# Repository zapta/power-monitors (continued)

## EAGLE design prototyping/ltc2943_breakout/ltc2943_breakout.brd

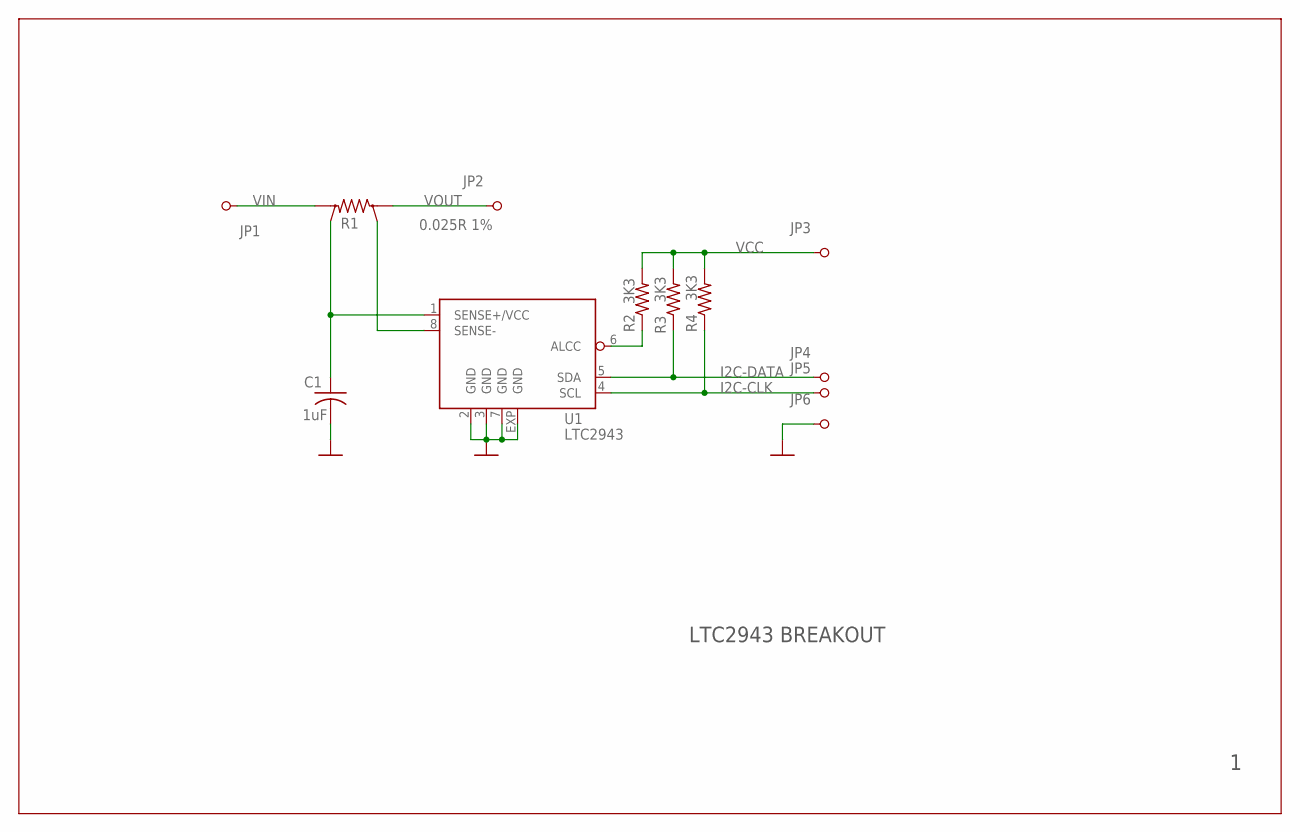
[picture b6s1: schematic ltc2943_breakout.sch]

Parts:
C1: 1uF; C0603
JP1, JP2, JP3, JP4, JP5, JP6: PINHD-1X1; 1X01
R1: 0.025R 1%; KELVIN-6432
R2, R3, R4: 3K3; R0603
U1: LTC2943; DFN8-3X3

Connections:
GND: C1.2, JP6.1, U1.2 (GND), U1.3 (GND), U1.7 (GND), U1.EXP (GND)
I2C-CLK: JP5.1, R4.1, U1.4 (SCL)
I2C-DATA: JP4.1, R3.1, U1.5 (SDA)
unnamed: R2.1, U1.6 (ALCC)
unnamed: R1.V1, U1.8 (SENSE-)
SENSE+: C1.1, R1.V2, U1.1 (SENSE+/VCC)
VCC: JP3.1, R2.2, R3.2, R4.2
VIN: JP1.1, R1.I2
VOUT: JP2.1, R1.I1

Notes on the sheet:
LTC2943 BREAKOUT

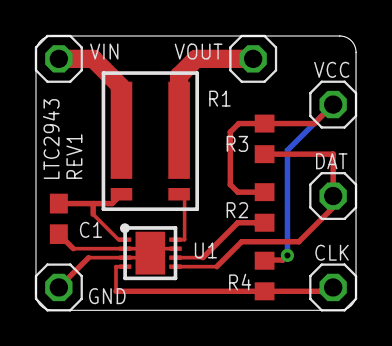
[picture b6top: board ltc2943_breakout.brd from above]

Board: 2 copper layers, 17.8 x 15.2 mm, 12 parts (0 on the bottom side), 9 nets.

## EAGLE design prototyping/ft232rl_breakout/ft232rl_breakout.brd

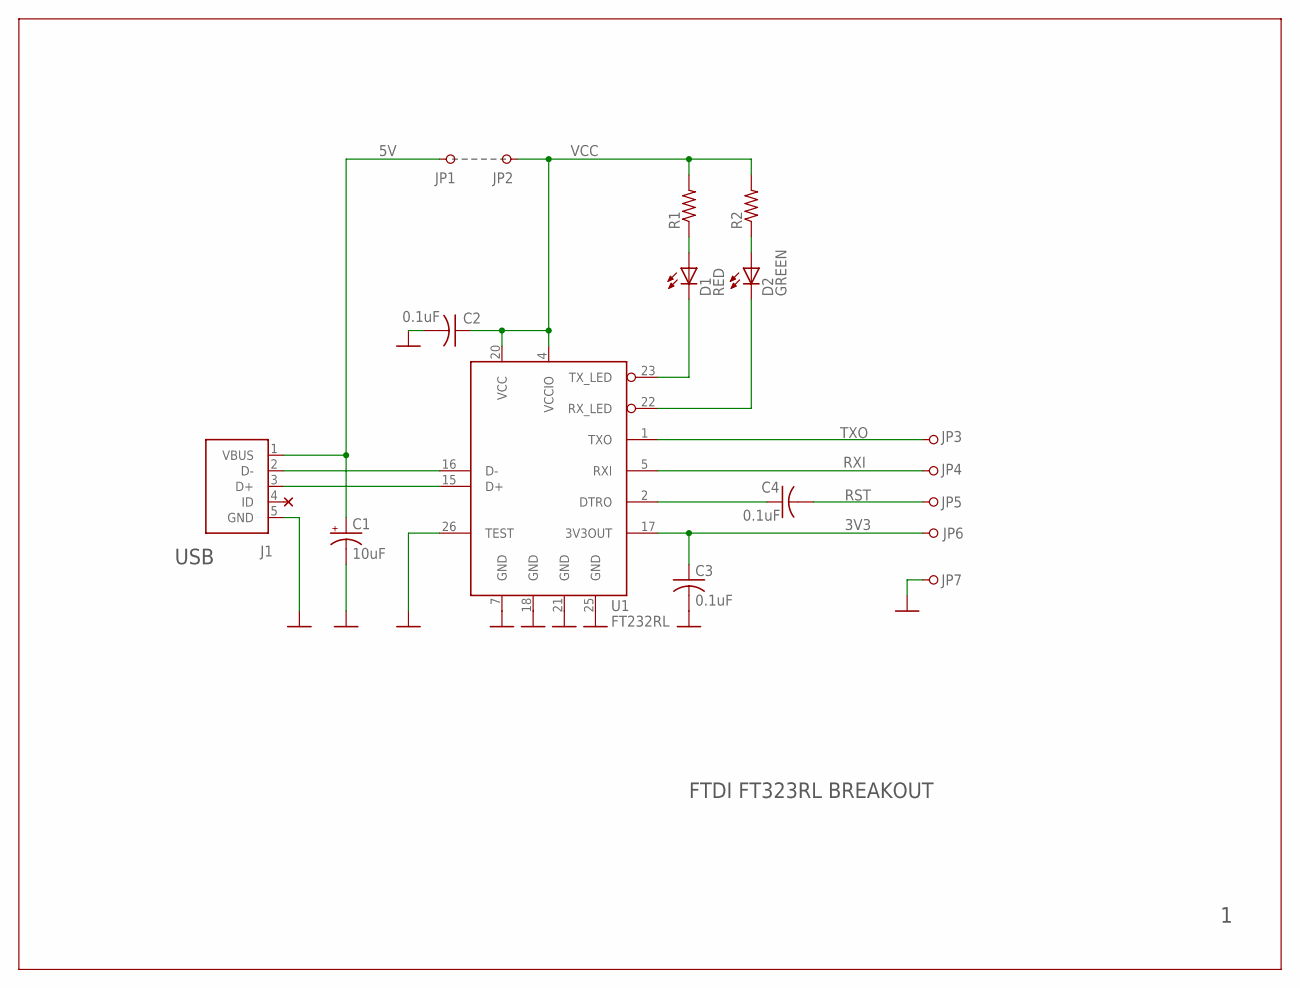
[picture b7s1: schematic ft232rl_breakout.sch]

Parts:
C1: 10uF; A/3216-18R
C2, C3, C4: 0.1uF; C0402K
D1: RED; LED_0402
D2: GREEN; LED_0402
J1: USB; USB-MICRO-ZX62RD-AB-5P8
JP1, JP2, JP3, JP4, JP5, JP6, JP7: PINHD-1X1; 1X01
R1, R2: R-US_R0402; R0402
U1: FT232RL; SSOP28DB

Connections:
3V3: C3.1, JP6.1, U1.17 (3V3OUT)
5V: C1.+, J1.1 (VBUS), JP1.1
GND: C1.-, C2.2, C3.2, J1.5 (GND), JP7.1, U1.7 (GND), U1.18 (GND), U1.21 (GND), U1.25 (GND), U1.26 (TEST)
unnamed: D1.C, U1.23 (TX_LED)
unnamed: D2.C, U1.22 (RX_LED)
unnamed: D1.A, R1.1
unnamed: D2.A, R2.1
unnamed: J1.3 (D+), U1.15 (D+)
unnamed: C4.1, U1.2 (DTRO)
unnamed: J1.2 (D-), U1.16 (D-)
RST: C4.2, JP5.1
RXI: JP4.1, U1.5 (RXI)
TXO: JP3.1, U1.1 (TXO)
VCC: C2.1, JP2.1, R1.2, R2.2, U1.4 (VCCIO), U1.20 (VCC)

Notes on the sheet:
FTDI FT323RL BREAKOUT
USB

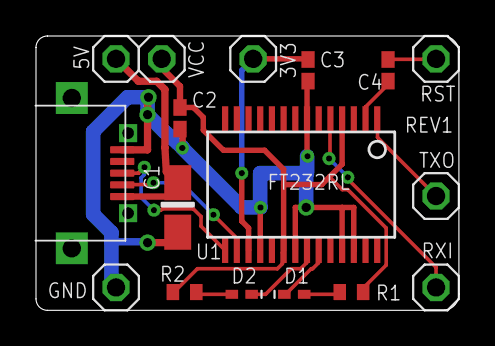
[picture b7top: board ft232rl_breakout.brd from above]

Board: 2 copper layers, 23.5 x 15.2 mm, 17 parts (0 on the bottom side), 14 nets.

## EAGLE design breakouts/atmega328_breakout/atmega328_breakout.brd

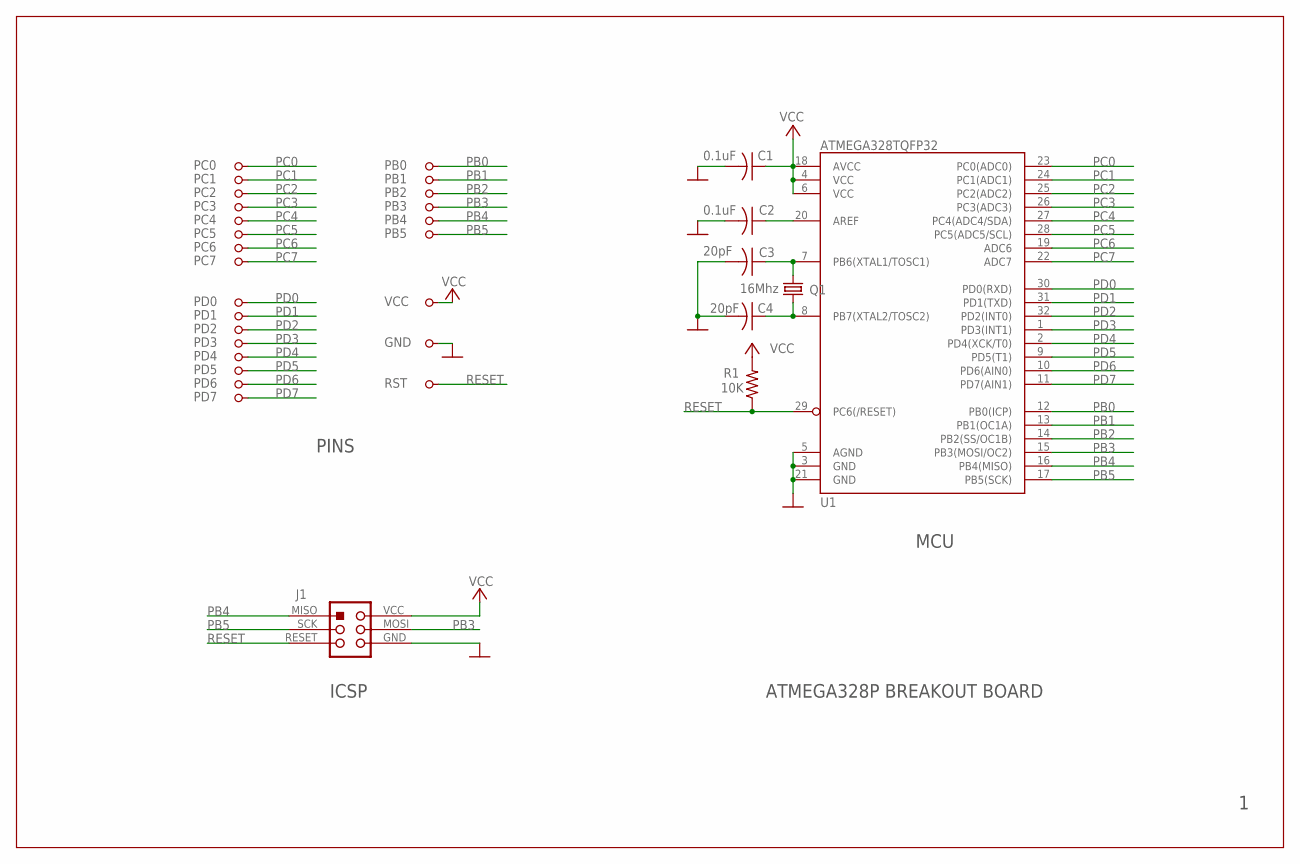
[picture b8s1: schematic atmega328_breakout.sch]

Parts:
C1, C2: 0.1uF; C0603
C3, C4: 20pF; C0603
GND: PINHD-1X1; 1X01
J1: ICSP
PB0, PB1, PB2, PB3, PB4, PB5: PINHD-1X1; 1X01
PC0, PC1, PC2, PC3, PC4, PC5, PC6, PC7: PINHD-1X1; 1X01
PD0, PD1, PD2, PD3, PD4, PD5, PD6, PD7: PINHD-1X1; 1X01
Q1: 16Mhz; CRYSTAL-CTS406
R1: 10K; R0603
RST: PINHD-1X1; 1X01
U1: ATMEGA328TQFP32; TQFP32-08
VCC: PINHD-1X1; 1X01

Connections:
AREF: C2.1, U1.20 (AREF)
GND: C1.2, C2.2, C3.2, C4.2, GND.1, J1.GND, U1.3 (GND), U1.5 (AGND), U1.21 (GND)
unnamed: C3.1, Q1.1, U1.7 (PB6(XTAL1/TOSC1))
unnamed: C4.1, Q1.3 (2), U1.8 (PB7(XTAL2/TOSC2))
PB0: PB0.1, U1.12 (PB0(ICP))
PB1: PB1.1, U1.13 (PB1(OC1A))
PB2: PB2.1, U1.14 (PB2(SS/OC1B))
PB3: J1.MOSI, PB3.1, U1.15 (PB3(MOSI/OC2))
PB4: J1.MISO, PB4.1, U1.16 (PB4(MISO))
PB5: J1.SCK, PB5.1, U1.17 (PB5(SCK))
PC0: PC0.1, U1.23 (PC0(ADC0))
PC1: PC1.1, U1.24 (PC1(ADC1))
PC2: PC2.1, U1.25 (PC2(ADC2))
PC3: PC3.1, U1.26 (PC3(ADC3))
PC4: PC4.1, U1.27 (PC4(ADC4/SDA))
PC5: PC5.1, U1.28 (PC5(ADC5/SCL))
PC6: PC6.1, U1.19 (ADC6)
PC7: PC7.1, U1.22 (ADC7)
PD0: PD0.1, U1.30 (PD0(RXD))
PD1: PD1.1, U1.31 (PD1(TXD))
PD2: PD2.1, U1.32 (PD2(INT0))
PD3: PD3.1, U1.1 (PD3(INT1))
PD4: PD4.1, U1.2 (PD4(XCK/T0))
PD5: PD5.1, U1.9 (PD5(T1))
PD6: PD6.1, U1.10 (PD6(AIN0))
PD7: PD7.1, U1.11 (PD7(AIN1))
RESET: J1.RESET, R1.1, RST.1, U1.29 (PC6(/RESET))
VCC: C1.1, J1.VCC, R1.2, U1.4 (VCC), U1.6 (VCC), U1.18 (AVCC), VCC.1

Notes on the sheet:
ATMEGA328P BREAKOUT BOARD
ICSP
PINS
MCU

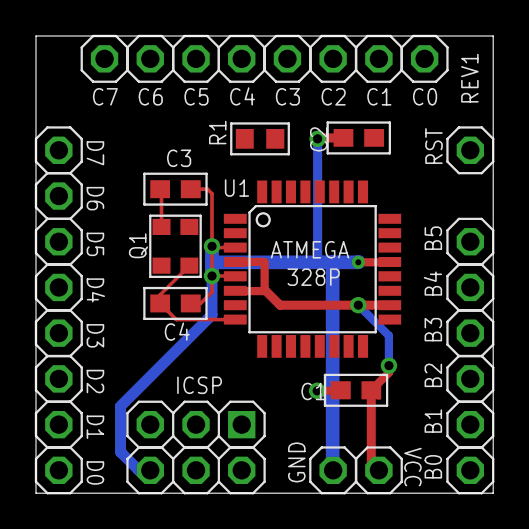
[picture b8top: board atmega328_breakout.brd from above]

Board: 2 copper layers, 25.4 x 25.4 mm, 33 parts (0 on the bottom side), 28 nets.

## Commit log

2014-04-19 Moved files from the temporary repository.
2014-04-19 Renamed eagle files from powermon.* t pmon_uno.*
2014-04-19 Removed the inversion of config input bits. Now using dipswitches that are active when open.
2014-04-19 Replaced dipswitch to through hole. Undone auto routing.
2014-04-19 Added hex image and script to program a blank Pmon Uno.
2014-04-19 Changed board fonts to vector, tweaked text. No final auto routing yet.
2014-04-20 Rearanged the leds pin to have a PWM option for the Status led.
2014-04-20 Layout completed.
2014-04-20 Added outline of a basic cover.
2014-04-20 Changed the button and power terminals to be top access (incremented to Rev B), Yet to be auto routed.
2014-04-21 Rev B is fully routed.
2014-04-21 Minor board tweak, adjusted via size.
2014-04-21 Changed the via stop limit from 20 to 30mils.
2014-04-21 Added laser cutting design for top and bottom covers.
2014-04-22 Cleaned up the LTC2943 formulas.
2014-04-22 Cleaned up the reporting.
2014-04-22 Handled truncation errors. Need to revisit.
2014-04-23 Started to cleanup the pmon uno BOM.
2014-04-23 Simplified the computations. Fixed the truncation errors.
2014-04-23 Tweaked the report message format.
2014-04-23 Added TODO list.
2014-04-24 Refactor the measurements and claculations. Now using a minor/major slot model.
2014-04-24 Refactored the slot tracking.
2014-04-25 Cleanedup the I2C code.
2014-04-25 Renamed 'data' to 'analysis'
2014-04-25 Minor Eagle tweaks: 1. Added a debug pin to the logic analyzer signals. 2. Changed the top and bottom drill sizes from 2.5mm to 3mm.
2014-04-26 Restored config switches polarity inversion due to hardware change.
2014-04-26 Added BOM.
2014-04-26 Renamed the bom file.
2014-04-29 Removed the timeout while waiting for I2C completion. According to the Atmel examples it is not required.
2014-04-29 Updated the pmon uno flash image.
2014-04-29 Added initial laser cut file (skeleton)
2014-05-03 Refactored the mode selection.
2014-05-03 Minor text tweaks. No semantic change.
2014-05-08 Updated schematic and board for rev c.
2014-05-08 Increased the dril of the USB connector two main support tabs.
2014-05-08 Respaced the LED row.
2014-05-08 Tweaked component labels.
2014-05-08 Added to top cover a cut for the power selector jumpers.
2014-05-09 Updated bom.
2014-05-10 Changed resistor values to reduce part SKU count. Selected different 1% resistor since the old ones did not have readable markings.
2014-05-10 Updated the BOM.
2014-05-10 Tweaked the mode table.
2014-05-11 OLED display test.
2014-05-12 Refactored the frimware to be more compatible with the Arduino libraries as a preperation for the U8Glib and OLED display.
2014-05-15 Minor cleanup.
2014-05-15 First checkin of the pmon OLED. This is a fork of the pmon UNO.
2014-05-15 Adjusted the logarithmic function of the displayed graph. Add more dynamic range at the high end (sub logarithmic).
2014-05-15 Added detection of button click and long press. Long press currently resets the analysis. Click will switch display pages in a later commit.
2014-05-15 Added a second display page (toggled by a button click).
2014-05-16 Added display messages. Still need to implement the rest (e.g. LTC2943 error message).
2014-05-16 Checkin in pending changes.
2014-05-17 Removed the errors led. Error message is now shown on the display.
2014-05-21 Routed critical networks. Ready for final auto routing.
2014-05-21 Minor board tweaks. Ready for final auto routing.
2014-05-21 Updated the layout for physical clearance.
2014-05-21 Tweaks criticla nets to improve auto rounting. Should be ready for final auto routing.
2014-05-21 Moved the bstop layer text up to the copper area.
2014-05-21 Beefed up a few power traces.
2014-05-21 Perfomed auto routing of non critical nets.
2014-05-21 Added pdf dumps of schematic and board layout.
2014-05-21 Adding an original gerber cam file from Seed. Will modify in latter commits.
2014-05-24 Added reading of output voltage. For now printing only in the Debug mode.
2014-05-25 Detailed report now prints also the voltage.
2014-05-25 Added reading of output voltage. Add a second summary screen with wake information.
2014-05-25 Updated .hex file to latest source code version.
2014-05-26 Changed reset capacitor from 0.01 to 0.1 (to reduce compoent kind count).
2014-05-27 Removed the concept of major vs minor slots. Now having only one kind. Changing reporting mode does not reset analysis anymore.
2014-05-27 Upshing pending oled changes.
2014-05-27 Deleted display test.
2014-05-27 Updated laser cut file.
2014-05-27 Added the version of u8glib that is known to work.
2014-05-27 Updated tools.
2014-05-27 Added test page for post assembly testing.
2014-05-27 Added 'gerber_' prefix to names of generated gerber files.
2014-05-28 Redesigned the OLED board to pass 5V through rather than regulating to 3.8. This way it can be sued with non instrumeted devices, feeding to the USB input (with some reduce accuracy due to charger st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
2014-05-29 Restoring the pmon_oled design with 3.8V regulator.
2014-05-29 Added bom for pmon_oled.
2014-05-30 Now entering test mode with long button press while power is applied.
2014-05-30 Removed temp files.
2014-05-30 Removed the config dip switches.
2014-05-30 Updated library (larger header pads) and auto rerouted.
2014-06-03 Added a 5V pass through version of pmon oled.
2014-06-03 Added pdf dumps of board and schematic.
2014-06-03 Performed the final auto routing.
2014-06-04 Cleaned up the board.
2014-06-04 Tweaked usb A support pads.
2014-06-04 Tweaked the test mode. Now can click the button without exiting test mode. Added display of LTC2943's charge register.
2014-06-04 Added firmware scripts for the pmon OLED.
2014-06-04 Made the dimension outline to have non zero width so it is shown in all gerber viewers.
2014-06-04 Minor doc changes.
2014-06-04 Updated the splash message.
2014-06-05 Removed power led, added vias to the solder jumpers.
2014-06-06 Removed PMpn UNO. Obsolete.
2014-06-06 Added pmon_5v BOM. Minor tweaks of schematics and layouts.
2014-06-06 Added repo license.
2014-06-06 Added a skeleton for the README file.
2014-06-06 Added diagrams.
2014-06-06 Renamed docs to doc.
2014-06-06 Test
2014-06-07 Test.
2014-06-07 Docs. Work in progress.
2014-06-12 More progress on the docs.
2014-06-12 Now displaying momentary current once a second instead of 10 times a second. This makes the display easier to read.
2014-06-12 Missing change from previous commiet.
2014-06-15 Firmware update: 1. Now displaying average current once a second (was 10 times a second). 2. Now displaying 1/10th of milliamps for momentary and average currets. 3. Overall spell check.
2014-06-15 Updated the hex file to latest firmware version.
2014-06-21 Updated the LTC2943 footpting to match the datasheet (longer pads now).
2014-06-21 Renamed power play oled to power play 3.8V (to be consistent with the 5V name of the other variant).
2014-06-21 Removed the generic gerber.cam. Not useful since we need to use vendor specific cam files anyway.
2014-06-21 Added a readme file for the u8glib library.
2014-06-21 Updated documentation to reflect the name change.
2014-06-23 Updated Power Play 3.8v documentation.
2014-06-23 Fixed file names.
2014-06-24 Spell check.
2014-06-24 Added repo level README.
2014-06-24 Fixed image links.
2014-06-24 Added readme file for pmon 5V.
2014-06-25 Added OLED reset pull down resistor.
2014-06-25 Added OLED reset pulldown resistor.
2014-06-26 Reduce startup delays. Reduce program side by eliminating rounded display frame function. Incremented version to 0.215. Updated .hex image.
2014-06-27 Updated OLED description in the BOM.
2014-06-28 Added serial in echo in Test mode.
2014-06-28 Added sh1106 datashet and electrow gerber cam job file.
2014-06-28 Seperated btween docs and www resources (images).
2014-06-28 Added ATMEGA328P datasheet.
2014-06-28 Added LTC2943 datasheet.
2014-06-29 Added datasheets.
2014-06-30 Added 4V regulator. Yet to do final auto routing.
2014-06-30 Performed final routing.
2014-06-30 Updated laser cut design files.
2014-07-01 Increased the paste area of the LTC2943.
2014-07-04 Original code, before modifications.
2014-07-10 ATMEGA328P breakout board. Ready for final auto routing.
2014-07-10 Pmon log, schematic. Work in progress.
2014-07-10 Fixed dimension to copper clearance.
2014-07-10 Cleaned up top silk layer.
2014-07-10 Updated ICSP silk and ground.
2014-07-11 Cleaned up laser cut files.
2014-07-13 Renamed +4V network to VCC. No semantic change.
2014-07-21 Renamed directory breakouts to prototyping
2014-07-22 Added FT232RL breakout. Ready for final auto routing.
2014-07-22 Updated the placement. Ready for final auto router.
2014-07-22 Performed final auto routing.
2014-07-22 Added PDF files.
2014-07-22 Added LTC2943 breakout board.
2014-07-23 Added a laser cut bracket for PCB stenciling.
2014-07-27 Minor layout change. Reroute a short between two pins to avoid reflow that looks like a solder bridge.
2014-07-30 First draft of micro sd breakout.
2014-07-30 Final routing of the microSD breakout board.
2014-07-30 Tweaked silk screen font size.
2014-08-01 Added tcream holes for usb connector tabs. Added bom.
2014-08-01 Add tcream holes for usb connector.
2014-08-01 Added tcream holes for usb connector tabs.
2014-08-01 Fixed firmware scripts. Now programming each fuze indepdently. Added status checks.
2014-08-01 Updated pdf schematic.
2014-08-04 Routed an air wire.
2014-08-04 Updated ltc2943 breakout board.
2014-08-04 Added pcb bracket.
2014-08-15 Updated doc titles.
2014-08-31 Added microscope mechanical bracket and PCB.
2014-08-31 Rename 'board' to 'pcb'
2014-09-07 Formated screen to display correctly voltages above 9.999V.
2014-09-07 Incremented version number to 1.00.
2014-09-07 Added a tiny bracket.
2014-09-10 Deleted prototyping directory. Moved to Misc repo.
2014-09-22 Added pdf schematic.
2015-01-07 Converted BOM to csv.
2015-01-08 Minor BOM fixes.
2015-01-08 Removed the PDF BOM (exported from Google Docs). Now using straight csv format for better upload to digikey.
2015-03-27 Converted the PDF BOM to CSV format.
2015-05-14 Added pmon 20V max. Yet to do final routing.
2015-05-16 Final tweaks.
2015-05-24 Added covers for pmon 20V
2015-05-24 Deleted obsolete files (moved)
2015-05-24 Removed open log.
2015-05-24 updated resistor part number to be 1%
2015-05-28 Now detecting reversed current. Also, fixed voltage display overflow for 10+ voltes.
2015-05-28 Tweaked error message.
